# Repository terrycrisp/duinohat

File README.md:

# DuinoHat
Design files for DuinoHat

Published on OSHpark at https://oshpark.com/shared_projects/P1rz4CnS

Hardware under OSHW-compliant MIT licence.

Current version: v2  
Primary files: 328_v2 (.brd/.sch)

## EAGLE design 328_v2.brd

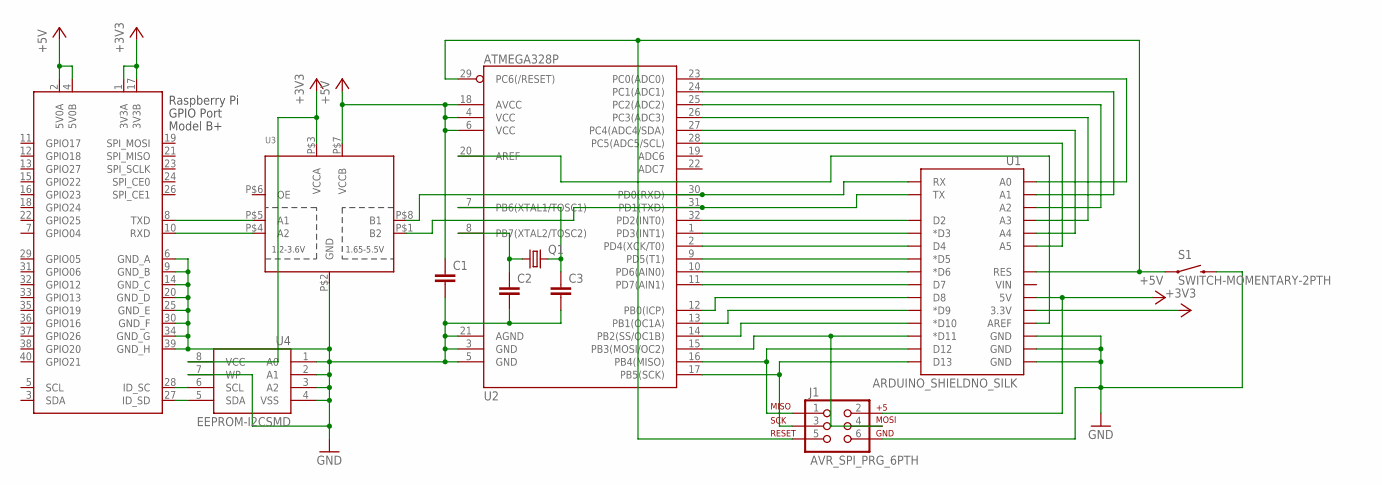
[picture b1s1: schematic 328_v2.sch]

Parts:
C1, C2, C3: C-EUC0805K; C0805K
J1: AVR_SPI_PRG_6PTH; 2X3
Q1: CRYSTALCTS406; CTS406
S1: SWITCH-MOMENTARY-2PTH; TACTILE-PTH
U1: ARDUINO_SHIELDNO_SILK; DUEMILANOVE_VIAS
U2: ATMEGA328P; TQFP32-08
U3: TXS0102; VFSOP-8
U4: EEPROM-I2CSMD; SO08
X1: RASPI_BOARD_B+#_H; RASPI_BOARD_B+HAT

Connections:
+3V3: U1.3.3V, U3.P$3 (VCCA), U4.8 (VCC), X1.1 (3V3A), X1.17 (3V3B)
+5V: C1.1, J1.2, U1.5V, U2.4 (VCC), U2.6 (VCC), U2.18 (AVCC), U3.P$7 (VCCB), X1.2 (5V0A), X1.4 (5V0B)
GND: C1.2, C2.2, C3.2, J1.6, S1.3 (2), U1.GND@0 (GND), U1.GND@1 (GND), U1.GND@2 (GND), U2.3 (GND), U2.5 (GND), U2.21 (AGND), U3.P$2 (GND), U4.1 (A0), U4.2 (A1), U4.3 (A2), U4.4 (VSS), U4.7 (WP), X1.6 (GND_A), X1.9 (GND_B), X1.14 (GND_C), X1.20 (GND_D), X1.25 (GND_E), X1.30 (GND_F), X1.34 (GND_G), X1.39 (GND_H)
unnamed: U3.P$5 (A1), X1.8 (TXD)
unnamed: U3.P$4 (A2), X1.10 (RXD)
unnamed: U1.RX, U2.30 (PD0(RXD)), U3.P$8 (B1)
unnamed: U1.TX, U2.31 (PD1(TXD)), U3.P$1 (B2)
unnamed: J1.1, U1.D12, U2.16 (PB4(MISO))
unnamed: U1.AREF, U2.20 (AREF)
unnamed: U1.D2, U2.32 (PD2(INT0))
unnamed: U1.D3 (*D3), U2.1 (PD3(INT1))
unnamed: U1.D4, U2.2 (PD4(XCK/T0))
unnamed: U1.D5 (*D5), U2.9 (PD5(T1))
unnamed: U1.D6 (*D6), U2.10 (PD6(AIN0))
unnamed: U1.D7, U2.11 (PD7(AIN1))
unnamed: U1.D8, U2.12 (PB0(ICP))
unnamed: U1.D9 (*D9), U2.13 (PB1(OC1A))
unnamed: U1.D10 (*D10), U2.14 (PB2(SS/OC1B))
unnamed: C3.1, Q1.3 (2), U2.7 (PB6(XTAL1/TOSC1))
unnamed: J1.4, U1.D11 (*D11), U2.15 (PB3(MOSI/OC2))
unnamed: J1.3, U1.D13, U2.17 (PB5(SCK))
unnamed: U1.A5, U2.28 (PC5(ADC5/SCL))
unnamed: U1.A4, U2.27 (PC4(ADC4/SDA))
unnamed: U1.A3, U2.26 (PC3(ADC3))
unnamed: U1.A2, U2.25 (PC2(ADC2))
unnamed: U1.A1, U2.24 (PC1(ADC1))
unnamed: U1.A0, U2.23 (PC0(ADC0))
unnamed: J1.5, S1.1, U1.RES, U2.29 (PC6(/RESET))
unnamed: U4.5 (SDA), X1.27 (ID_SD)
unnamed: U4.6 (SCL), X1.28 (ID_SC)
unnamed: C2.1, Q1.1, U2.8 (PB7(XTAL2/TOSC2))

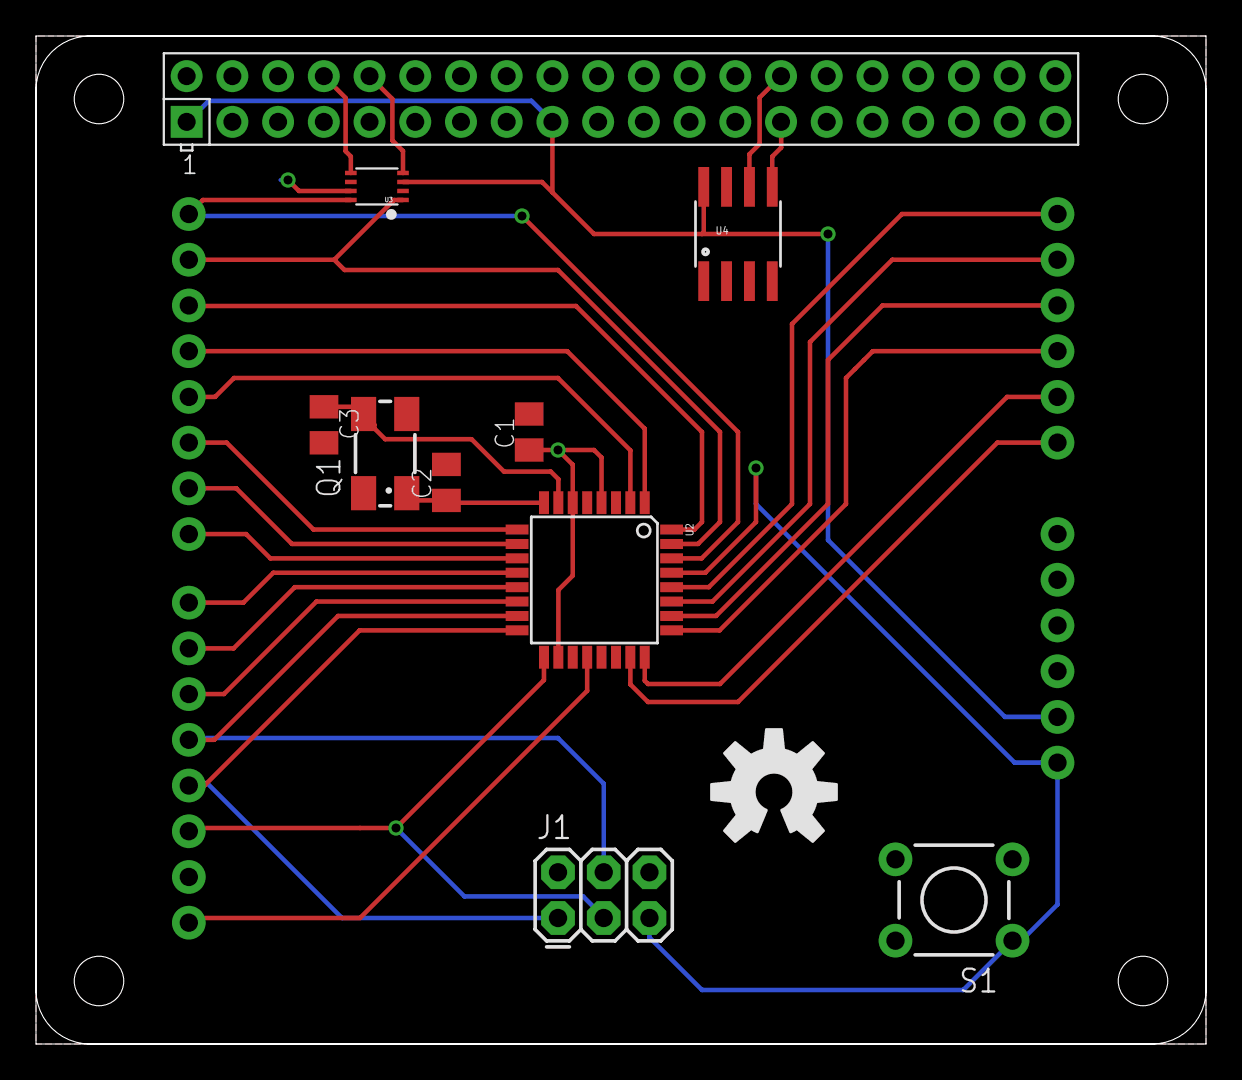
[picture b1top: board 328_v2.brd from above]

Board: 2 copper layers, 65.0 x 56.0 mm, 12 parts (0 on the bottom side), 31 nets.

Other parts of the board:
U$1: OSHW-LOGO-L

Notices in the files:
328_v2.brd:
(C) 2016 Terence Crisp
parts and their libraries:
SparkFun-Boards: Licensing: Creative Commons ShareAlike 4.0 International - https://creativecommons.org/licenses/by-sa/4.0
